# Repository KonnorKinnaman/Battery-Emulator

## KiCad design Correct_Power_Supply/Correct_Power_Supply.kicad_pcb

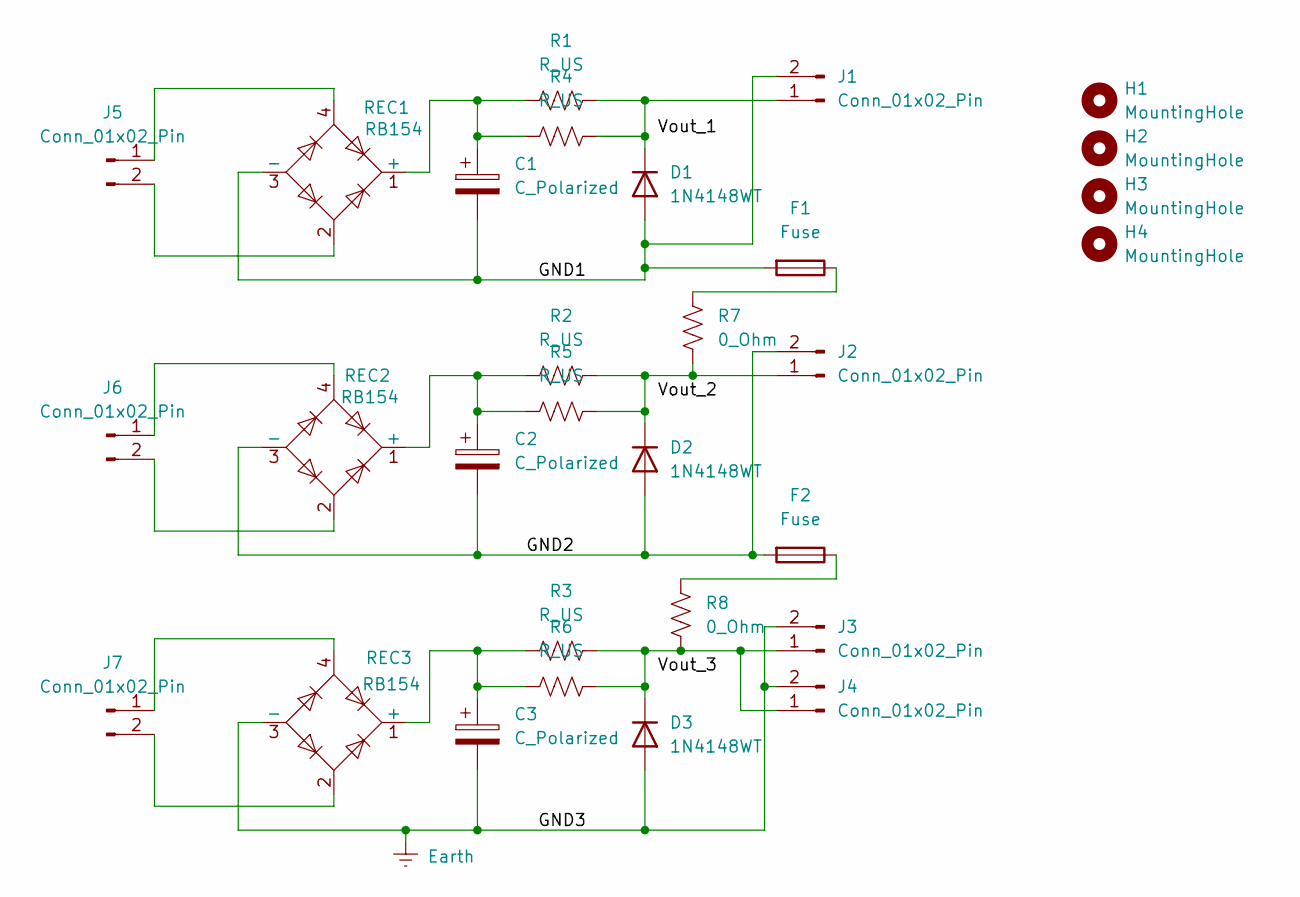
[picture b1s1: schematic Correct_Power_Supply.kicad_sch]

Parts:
C1, C2, C3: C_Polarized; CP_Radial_D8.0mm_P5.00mm
D1, D2, D3: 1N4148WT; D_A-405_P7.62mm_Horizontal
F1, F2: Fuse; SS5H2AAPH
H1, H2, H3, H4: MountingHole; MountingHole_2.2mm_M2_DIN965_Pad
J1, J2, J3, J4, J5, J6, J7: Conn_01x02_Pin; PinHeader_1x02_P2.54mm_Vertical
R1, R2, R3, R4, R5, R6: R_US; R_Axial_DIN0204_L3.6mm_D1.6mm_P5.08mm_Horizontal
R7, R8: 0_Ohm; R_Axial_DIN0204_L3.6mm_D1.6mm_P5.08mm_Horizontal
REC1, REC2, REC3: RB154; Diode_Bridge_Round_D9.0mm

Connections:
/GND1: C1.2, D1.2 (A), F1.2, J1.2, REC1.3 (-)
/GND2: C2.2, D2.2 (A), F2.2, J2.2, REC2.3 (-)
Earth: C3.2, D3.2 (A), J3.2, J4.2, REC3.3 (-)
unnamed: D1.1 (K), J1.1, R1.1, R4.1
unnamed: D2.1 (K), J2.1, R2.1, R5.1, R7.1
unnamed: D3.1 (K), J3.1, J4.1, R3.1, R6.1, R8.1
unnamed: F1.1, R7.2
unnamed: F2.1, R8.2
unnamed: J5.1, REC1.4
unnamed: J5.2, REC1.2
unnamed: J6.1, REC2.4
unnamed: J6.2, REC2.2
unnamed: J7.1, REC3.4
unnamed: J7.2, REC3.2
unnamed: C1.1, R1.2, R4.2, REC1.1 (+)
unnamed: C2.1, R2.2, R5.2, REC2.1 (+)
unnamed: C3.1, R3.2, R6.2, REC3.1 (+)

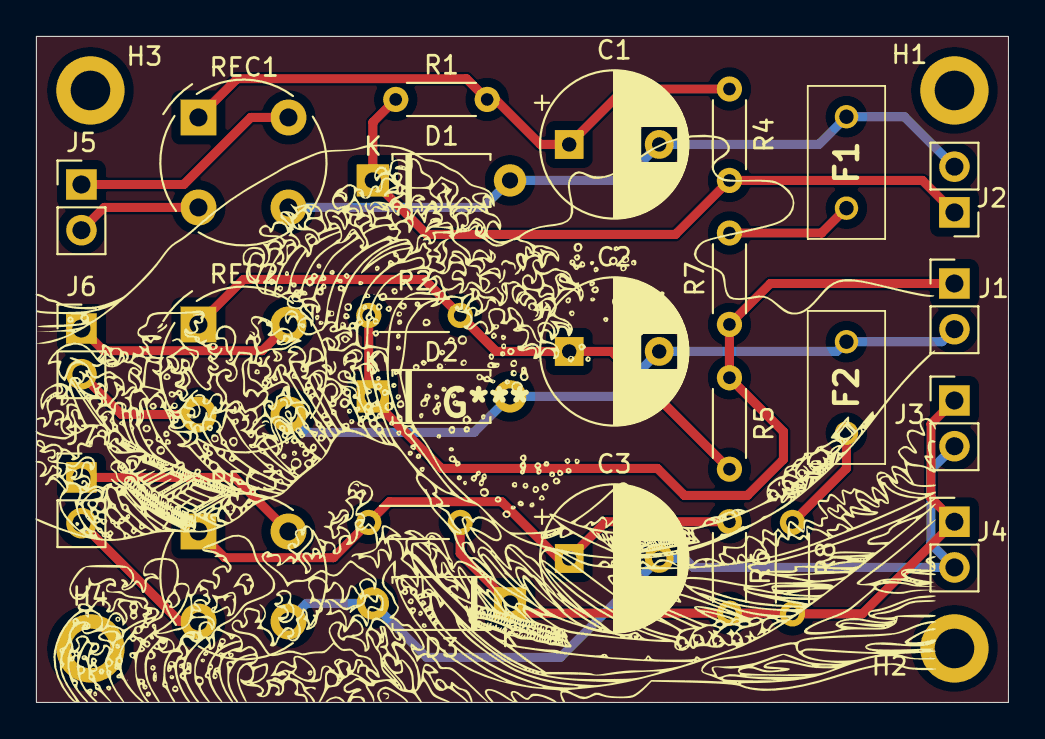
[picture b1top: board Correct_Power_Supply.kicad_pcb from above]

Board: 2 copper layers, 54.0 x 37.0 mm, 30 parts (0 on the bottom side), 17 nets.

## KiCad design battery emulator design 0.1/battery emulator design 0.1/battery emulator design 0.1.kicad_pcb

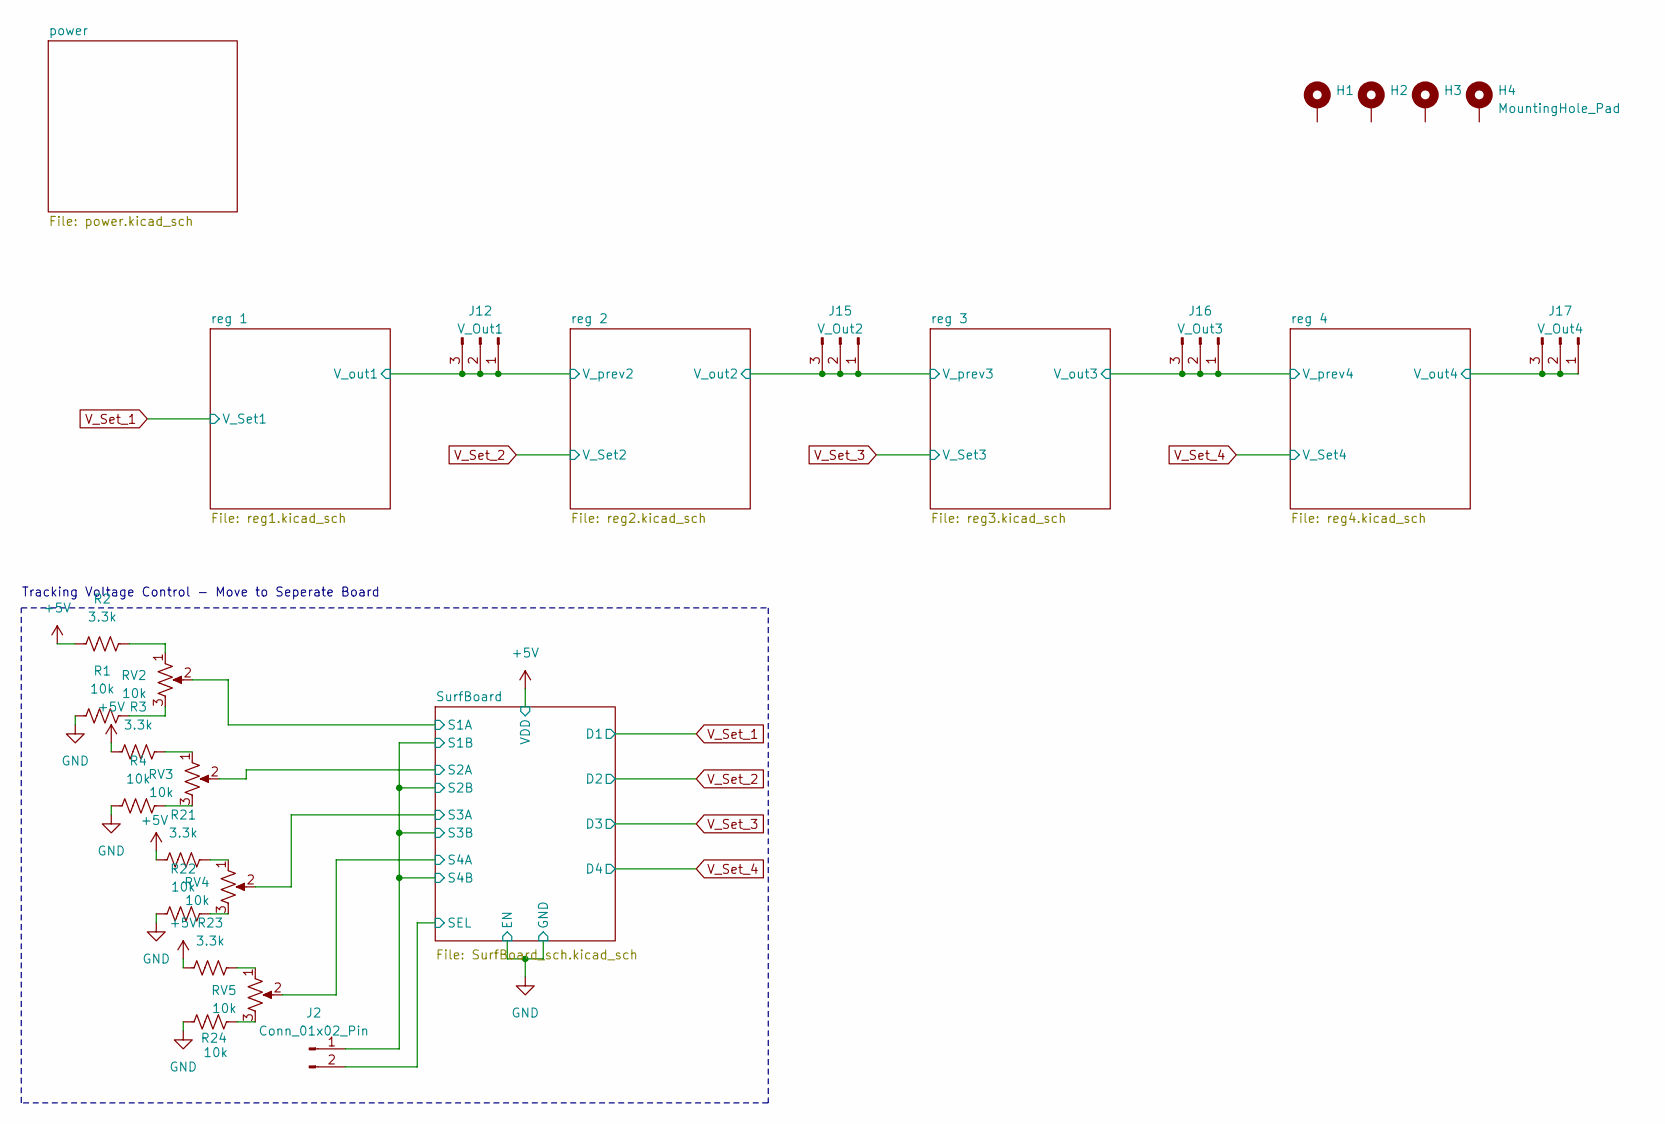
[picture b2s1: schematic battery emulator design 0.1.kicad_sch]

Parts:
H1, H2, H3, H4: MountingHole_Pad; MountingHole_4.3mm_M4_Pad
J2: Conn_01x02_Pin; PinHeader_1x02_P2.54mm_Vertical
J12: V_Out1; PinHeader_1x03_P2.54mm_Vertical
J15: V_Out2; PinHeader_1x03_P2.54mm_Vertical
J16: V_Out3; PinHeader_1x03_P2.54mm_Vertical
J17: V_Out4; PinHeader_1x03_P2.54mm_Vertical
R1, R4, R22, R24: 10k; R_Axial_DIN0207_L6.3mm_D2.5mm_P10.16mm_Horizontal
R2, R3, R21, R23: 3.3k; R_Axial_DIN0207_L6.3mm_D2.5mm_P10.16mm_Horizontal
RV2, RV3, RV4, RV5: 10k; PDB181

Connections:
+5V: R2.2, R3.2, R21.2, R23.2; also elsewhere on the board
/SurfBoard/S1A: RV2.2; also elsewhere on the board
/SurfBoard/S1B: J2.1; also elsewhere on the board
/SurfBoard/S2A: RV3.2; also elsewhere on the board
/SurfBoard/S3A: RV4.2; also elsewhere on the board
/SurfBoard/S4A: RV5.2; also elsewhere on the board
/SurfBoard/SEL: J2.2; also elsewhere on the board
/reg 1/V_out1: J12.1, J12.2, J12.3; also elsewhere on the board
/reg 2/V_out2: J15.1, J15.2, J15.3; also elsewhere on the board
/reg 3/V_out3: J16.1, J16.2, J16.3; also elsewhere on the board
/reg 4/V_out4: J17.1, J17.2, J17.3; also elsewhere on the board
GND: R1.2, R4.2, R22.2, R24.2; also elsewhere on the board
unnamed: R1.1, RV2.3
unnamed: R2.1, RV2.1
unnamed: R3.1, RV3.1
unnamed: R4.1, RV3.3
unnamed: R21.1, RV4.1
unnamed: R22.1, RV4.3
unnamed: R23.1, RV5.1
unnamed: R24.1, RV5.3

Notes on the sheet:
Tracking Voltage Control - Move to Seperate Board

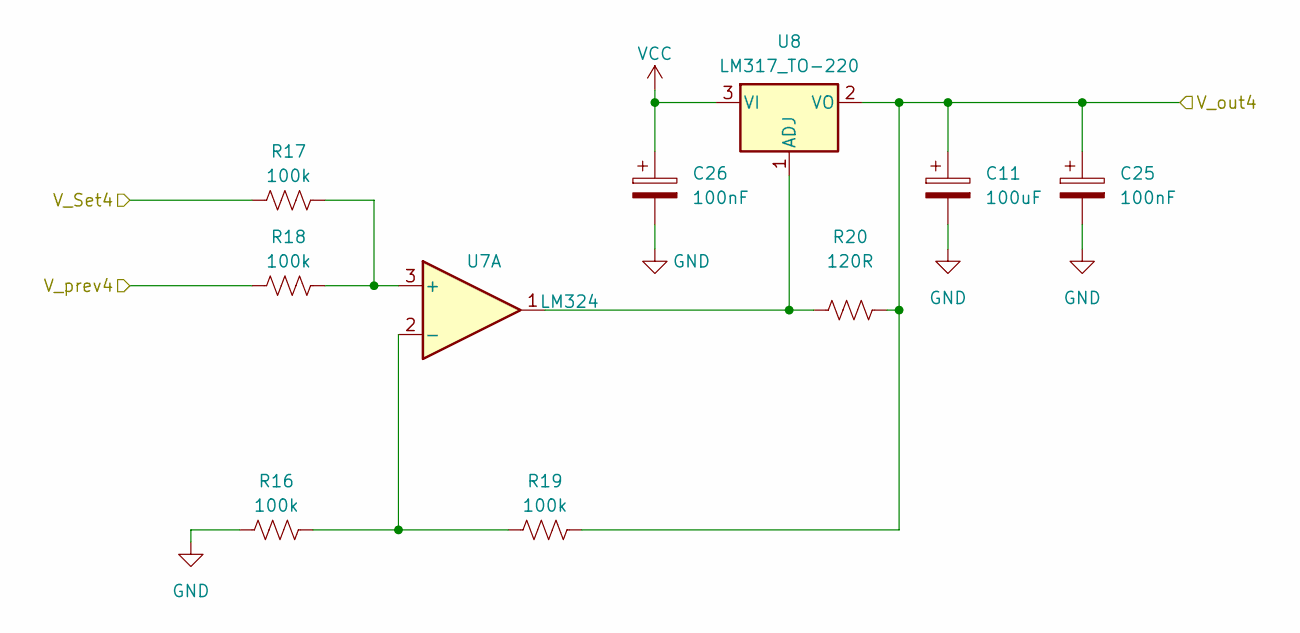
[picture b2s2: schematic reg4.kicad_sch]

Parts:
C11: 100uF; CP_Radial_D7.5mm_P2.50mm
C25, C26: 100nF; C_Disc_D3.4mm_W2.1mm_P2.50mm
R16, R17, R18, R19: 100k; R_Axial_DIN0207_L6.3mm_D2.5mm_P10.16mm_Horizontal
R20: 120R; R_Axial_DIN0207_L6.3mm_D2.5mm_P10.16mm_Horizontal
U7: LM324; DIP-8_W7.62mm_LongPads
U8: LM317_TO-220; TO-220-3_Vertical

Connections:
/reg 3/V_out3: R18.1; also elsewhere on the board
/reg 4/V_out4: C11.1, C25.1, R19.2, R20.1, U8.2 (VO); also elsewhere on the board
GND: C11.2, C25.2, C26.2, R16.1; also elsewhere on the board
unnamed 26: R17.2, R18.2, U7.3 (+); also elsewhere on the board
unnamed 27: R16.2, R19.1, U7.2 (-); also elsewhere on the board
unnamed 31: R20.2, U7.1, U8.1 (ADJ); also elsewhere on the board
VCC: C26.1, U8.3 (VI); also elsewhere on the board
V_Set_4: R17.1; also elsewhere on the board

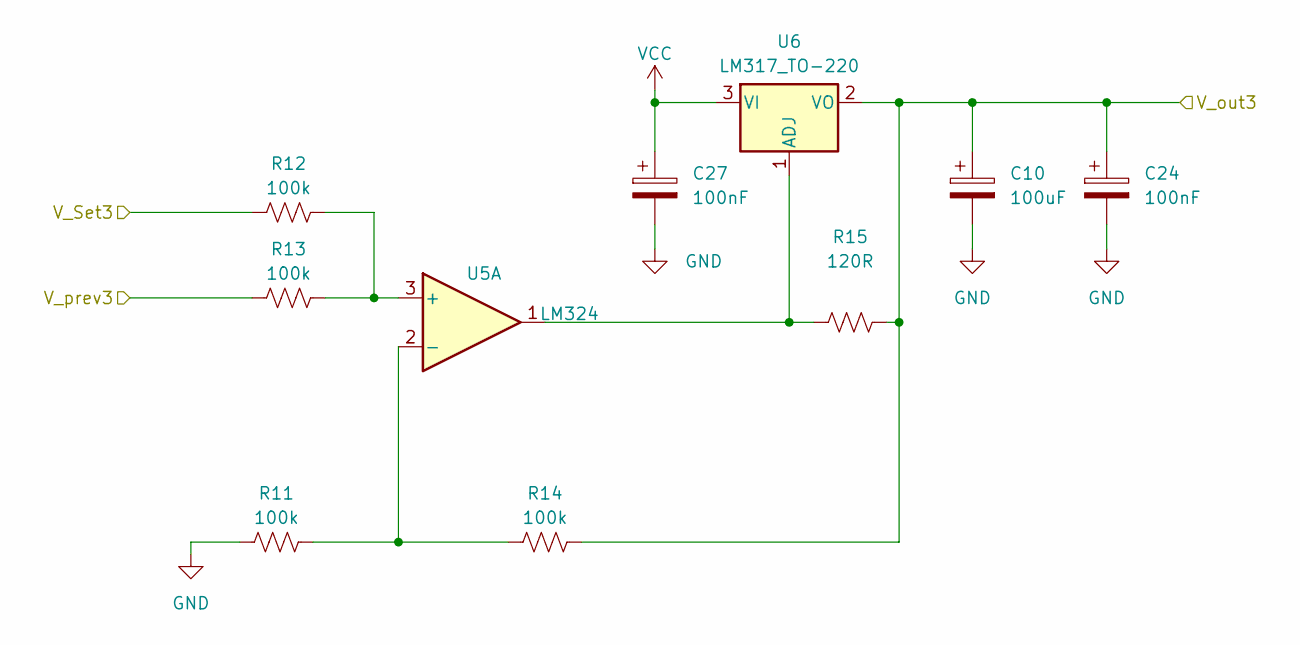
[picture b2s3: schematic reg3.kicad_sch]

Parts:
C10: 100uF; CP_Radial_D7.5mm_P2.50mm
C24, C27: 100nF; C_Disc_D3.4mm_W2.1mm_P2.50mm
R11, R12, R13, R14: 100k; R_Axial_DIN0207_L6.3mm_D2.5mm_P10.16mm_Horizontal
R15: 120R; R_Axial_DIN0207_L6.3mm_D2.5mm_P10.16mm_Horizontal
U5: LM324; DIP-8_W7.62mm_LongPads
U6: LM317_TO-220; TO-220-3_Vertical

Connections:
/reg 2/V_out2: R13.1; also elsewhere on the board
/reg 3/V_out3: C10.1, C24.1, R14.2, R15.1, U6.2 (VO); also elsewhere on the board
GND: C10.2, C24.2, C27.2, R11.1; also elsewhere on the board
unnamed 24: R12.2, R13.2, U5.3 (+); also elsewhere on the board
unnamed 25: R11.2, R14.1, U5.2 (-); also elsewhere on the board
unnamed 30: R15.2, U5.1, U6.1 (ADJ); also elsewhere on the board
VCC: C27.1, U6.3 (VI); also elsewhere on the board
V_Set_3: R12.1; also elsewhere on the board

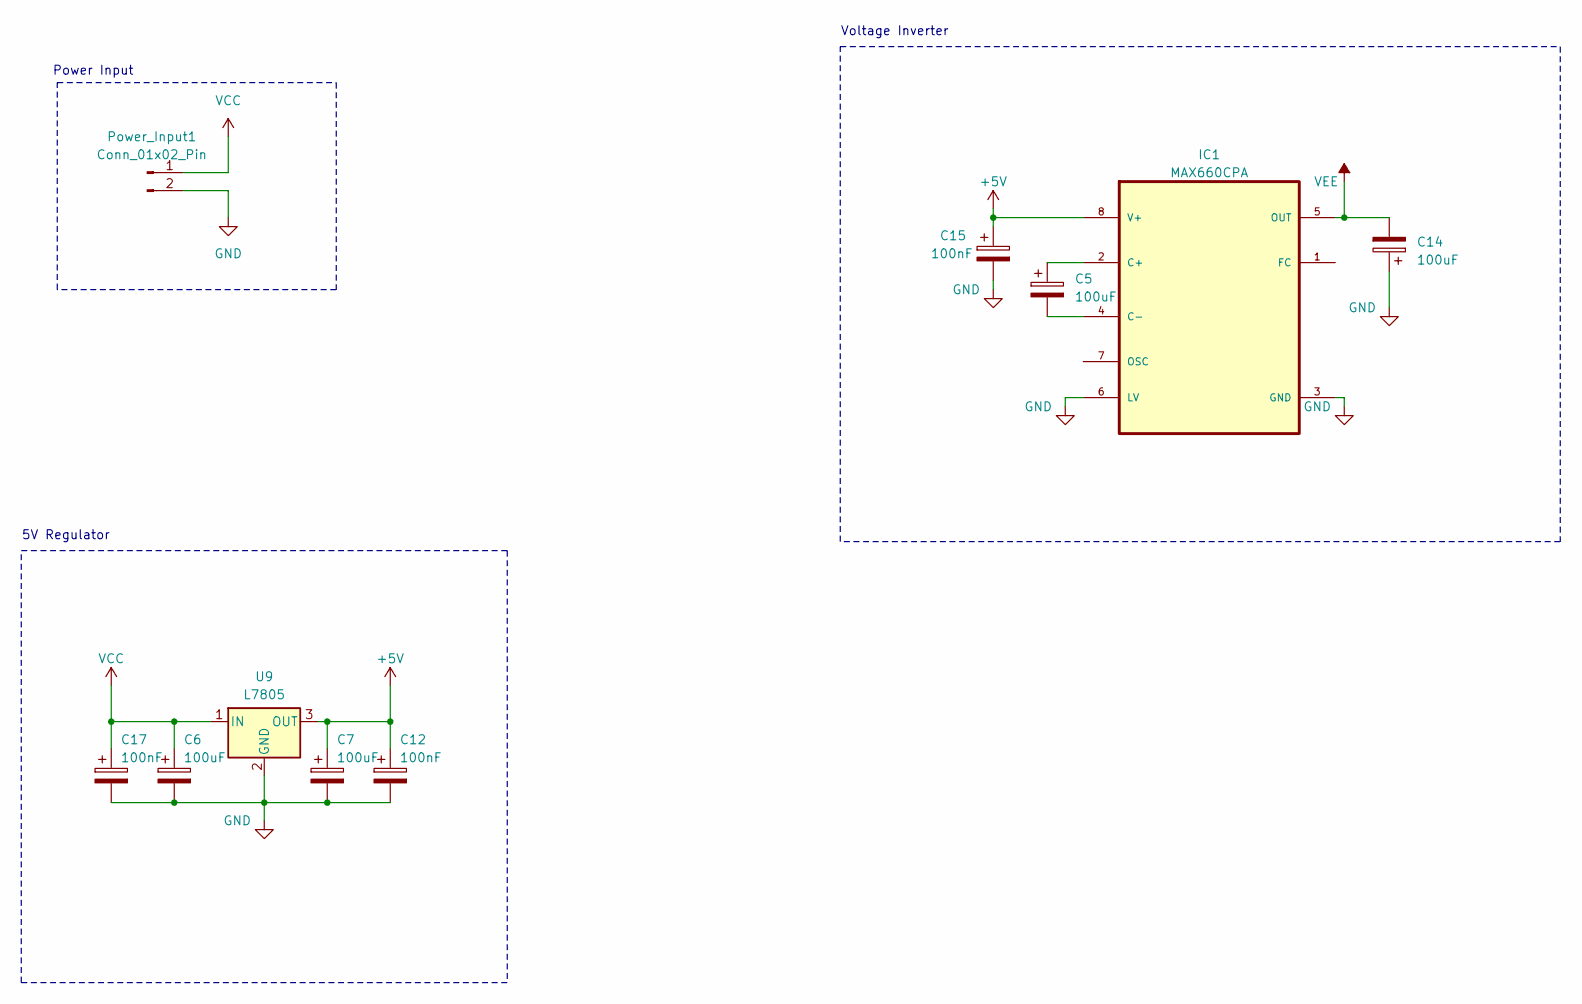
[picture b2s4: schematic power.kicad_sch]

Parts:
C5, C6, C7, C14: 100uF; CP_Radial_D7.5mm_P2.50mm
C12, C15, C17: 100nF; C_Disc_D4.3mm_W1.9mm_P5.00mm
IC1: MAX660CPA; DIP-8_W7.62mm_LongPads
Power_Input1: Conn_01x02_Pin; PinHeader_1x02_P2.54mm_Vertical
U9: L7805; TO-220-3_Vertical

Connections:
+5V: C7.1, C12.1, C15.1, IC1.8 (V+), U9.3 (OUT); also elsewhere on the board
GND: C6.2, C7.2, C12.2, C14.1, C15.2, C17.2, IC1.3 (GND), IC1.6 (LV), Power_Input1.2, U9.2 (GND); also elsewhere on the board
unnamed: C5.1, IC1.2 (C+)
unnamed: C5.2, IC1.4 (C-)
VCC: C6.1, C17.1, Power_Input1.1, U9.1 (IN); also elsewhere on the board
VEE: C14.2, IC1.5 (OUT); also elsewhere on the board

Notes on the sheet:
Voltage Inverter
5V Regulator
Power Input

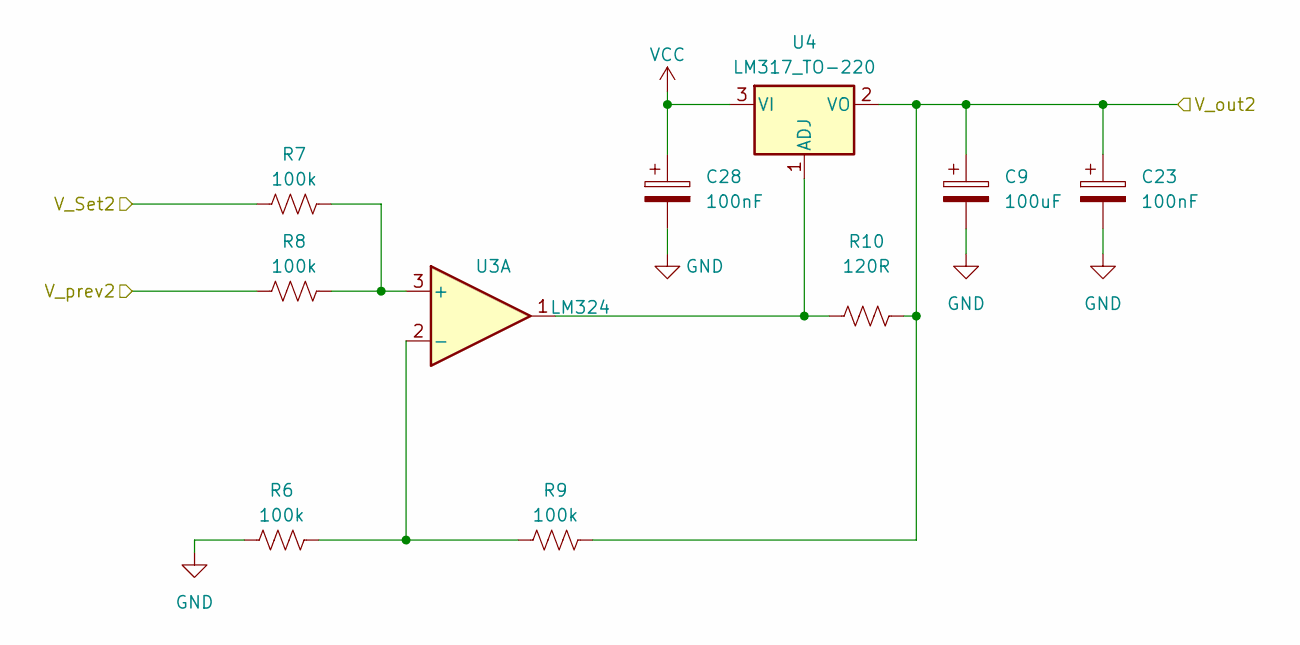
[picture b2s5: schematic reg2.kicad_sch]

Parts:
C9: 100uF; CP_Radial_D7.5mm_P2.50mm
C23, C28: 100nF; C_Disc_D3.4mm_W2.1mm_P2.50mm
R6, R7, R8, R9: 100k; R_Axial_DIN0207_L6.3mm_D2.5mm_P10.16mm_Horizontal
R10: 120R; R_Axial_DIN0207_L6.3mm_D2.5mm_P10.16mm_Horizontal
U3: LM324; DIP-8_W7.62mm_LongPads
U4: LM317_TO-220; TO-220-3_Vertical

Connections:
/reg 1/V_out1: R8.1; also elsewhere on the board
/reg 2/V_out2: C9.1, C23.1, R9.2, R10.1, U4.2 (VO); also elsewhere on the board
GND: C9.2, C23.2, C28.2, R6.1; also elsewhere on the board
unnamed 22: R7.2, R8.2, U3.3 (+); also elsewhere on the board
unnamed 23: R6.2, R9.1, U3.2 (-); also elsewhere on the board
unnamed 29: R10.2, U3.1, U4.1 (ADJ); also elsewhere on the board
VCC: C28.1, U4.3 (VI); also elsewhere on the board
V_Set_2: R7.1; also elsewhere on the board

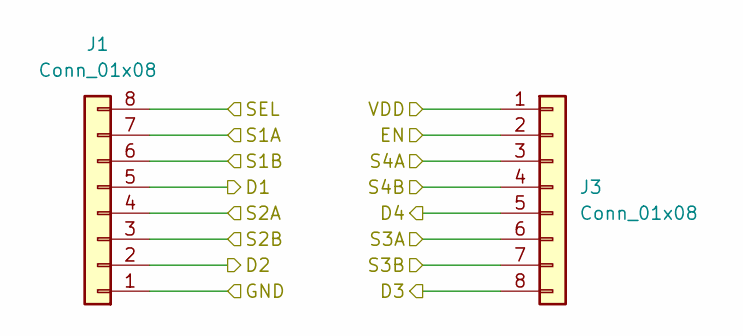
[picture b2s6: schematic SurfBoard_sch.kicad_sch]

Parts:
J1, J3: Conn_01x08; PinSocket_1x08_P2.54mm_Vertical

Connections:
+5V: J3.1; also elsewhere on the board
/SurfBoard/S1A: J1.7; also elsewhere on the board
/SurfBoard/S1B: J1.3, J1.6, J3.4, J3.7; also elsewhere on the board
/SurfBoard/S2A: J1.4; also elsewhere on the board
/SurfBoard/S3A: J3.6; also elsewhere on the board
/SurfBoard/S4A: J3.3; also elsewhere on the board
/SurfBoard/SEL: J1.8; also elsewhere on the board
GND: J1.1, J3.2; also elsewhere on the board
V_Set_1: J1.5; also elsewhere on the board
V_Set_2: J1.2; also elsewhere on the board
V_Set_3: J3.8; also elsewhere on the board
V_Set_4: J3.5; also elsewhere on the board

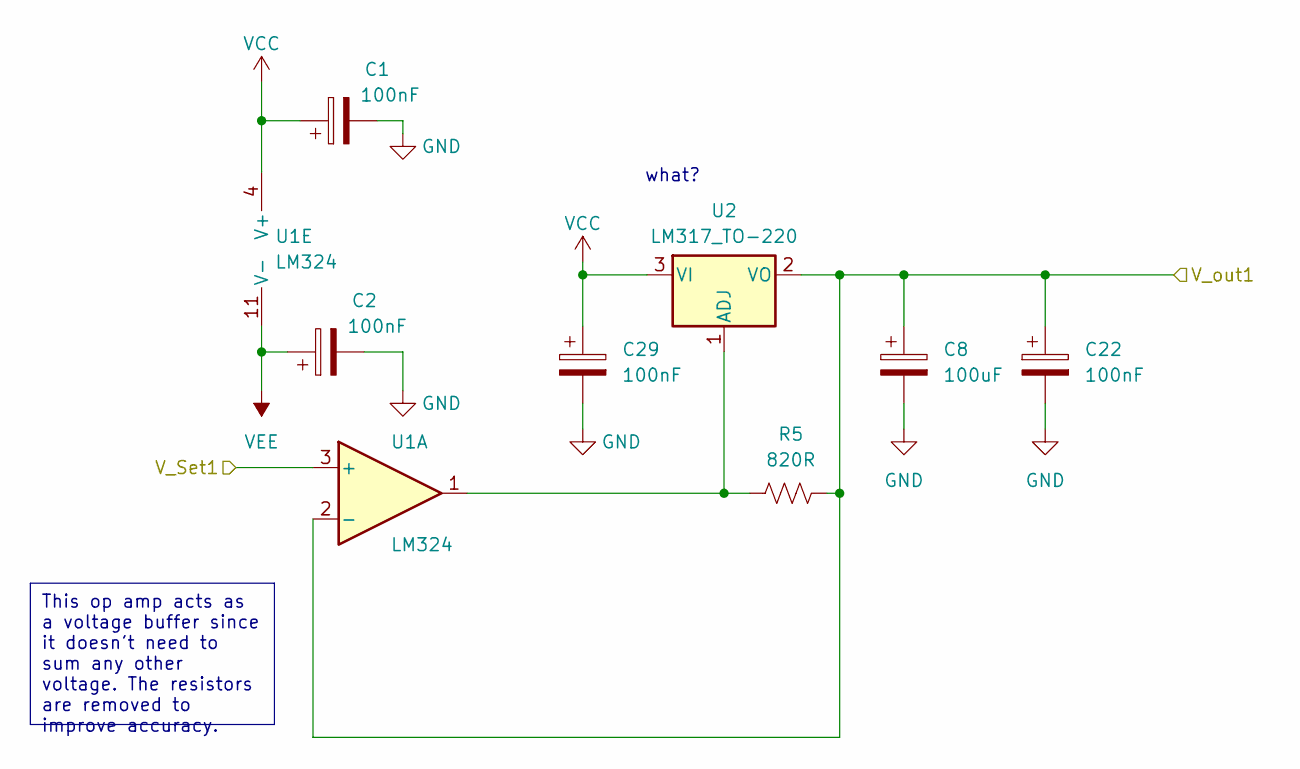
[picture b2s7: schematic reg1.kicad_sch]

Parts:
C1, C2, C22, C29: 100nF; C_Disc_D3.4mm_W2.1mm_P2.50mm
C8: 100uF; CP_Radial_D7.5mm_P2.50mm
R5: 820R; R_Axial_DIN0207_L6.3mm_D2.5mm_P10.16mm_Horizontal
U1: LM324; DIP-8_W7.62mm_LongPads
U2: LM317_TO-220; TO-220-3_Vertical

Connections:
/reg 1/V_out1: C8.1, C22.1, R5.1, U1.2 (-), U2.2 (VO); also elsewhere on the board
GND: C1.2, C2.2, C8.2, C22.2, C29.2; also elsewhere on the board
unnamed 22: U1.5 (+); also elsewhere on the board
unnamed 23: U1.6 (-); also elsewhere on the board
unnamed 24: U1.10 (+); also elsewhere on the board
unnamed 25: U1.9 (-); also elsewhere on the board
unnamed 26: U1.12 (+); also elsewhere on the board
unnamed 27: U1.13 (-); also elsewhere on the board
unnamed: R5.2, U1.1, U2.1 (ADJ)
unnamed 29: U1.7; also elsewhere on the board
unnamed 30: U1.8; also elsewhere on the board
unnamed 31: U1.14; also elsewhere on the board
VCC: C1.1, C29.1, U1.4 (V+), U2.3 (VI); also elsewhere on the board
VEE: C2.1, U1.11 (V-); also elsewhere on the board
V_Set_1: U1.3 (+); also elsewhere on the board

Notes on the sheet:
This op amp acts as a voltage buffer since it doesn't need to sum any other voltage. The resistors are removed to improve accuracy.
what?

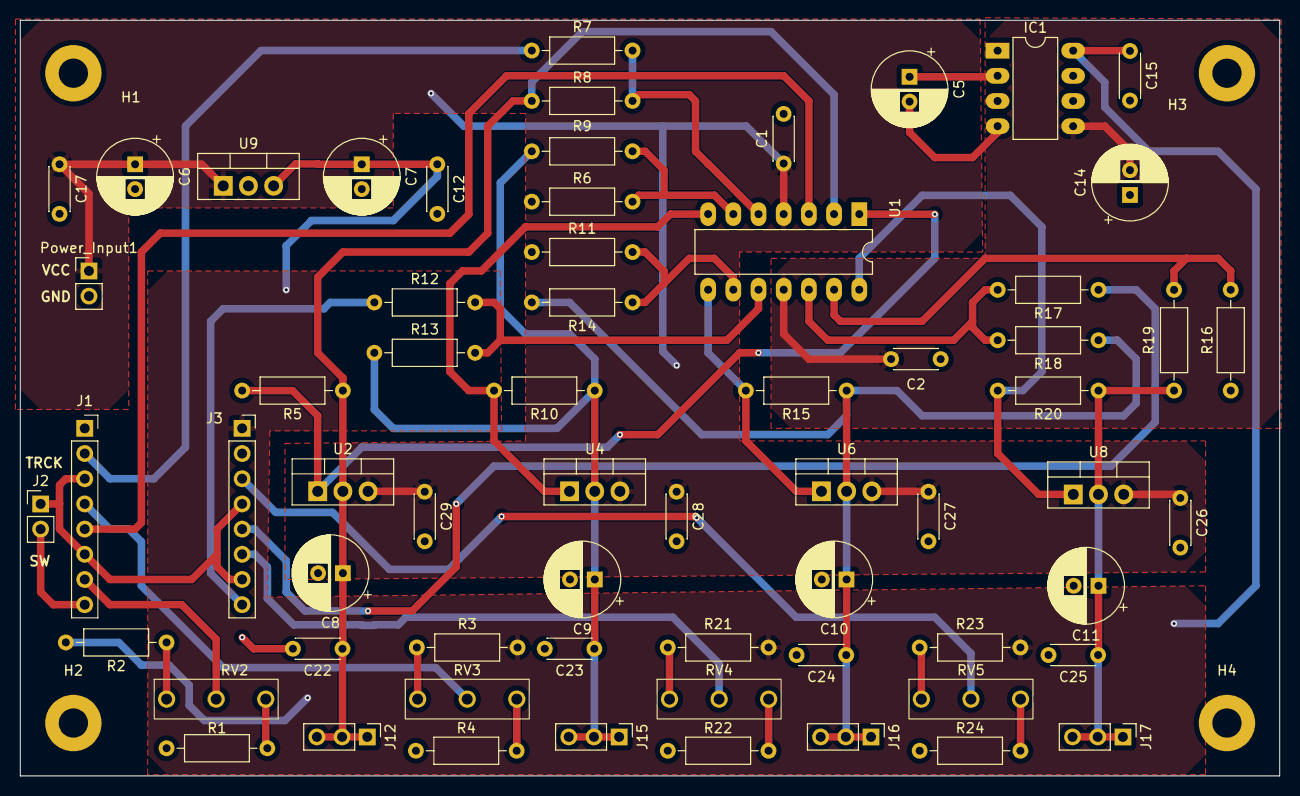
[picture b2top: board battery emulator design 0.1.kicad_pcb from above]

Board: 2 copper layers, 127.0 x 76.2 mm, 68 parts (0 on the bottom side), 38 nets.

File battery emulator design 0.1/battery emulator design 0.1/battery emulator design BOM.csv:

Reference,Value,Datasheet,Footprint,Qty,DNP
"C1,C2,C12,C15,C17,C22,C23,C24,C25,C26,C27,C28,C29",100nF,~,Capacitor_THT:C_Disc_D4.3mm_W1.9mm_P5.00mm,13,
"C5,C6,C7,C8,C9,C10,C11,C14",100uF,~,Capacitor_THT:CP_Radial_D7.5mm_P2.50mm,8,
"H1,H2,H3,H4",MountingHole_Pad,~,MountingHole:MountingHole_4.3mm_M4_Pad,4,
IC1,MAX660CPA,,Package_DIP:DIP-8_W7.62mm_LongPads,1,
"J1,J3",Conn_01x08,~,Connector_PinSocket_2.54mm:PinSocket_1x08_P2.54mm_Vertical,2,
"J2,Power_Input1",Conn_01x02_Pin,~,Connector_PinHeader_2.54mm:PinHeader_1x02_P2.54mm_Vertical,2,
J12,V_Out1,~,Connector_PinHeader_2.54mm:PinHeader_1x03_P2.54mm_Vertical,1,
J15,V_Out2,~,Connector_PinHeader_2.54mm:PinHeader_1x03_P2.54mm_Vertical,1,
J16,V_Out3,~,Connector_PinHeader_2.54mm:PinHeader_1x03_P2.54mm_Vertical,1,
J17,V_Out4,~,Connector_PinHeader_2.54mm:PinHeader_1x03_P2.54mm_Vertical,1,
"R1,R4,R22,R24,RV2,RV3,RV4,RV5",10k,~,"Resistor_THT:R_Axial_DIN0207_L6.3mm_D2.5mm_P10.16mm_Horizontal,battery_emulator:PDB181",8,
"R2,R3,R21,R23",3.3k,~,Resistor_THT:R_Axial_DIN0207_L6.3mm_D2.5mm_P10.16mm_Horizontal,4,
"R5,R10,R15,R20",150,~,Resistor_THT:R_Axial_DIN0207_L6.3mm_D2.5mm_P10.16mm_Horizontal,1,
"R6,R7,R8,R9,R11,R12,R13,R14,R16,R17,R18,R19",100k,~,Resistor_THT:R_Axial_DIN0207_L6.3mm_D2.5mm_P10.16mm_Horizontal,12,
U1,LM324,http://www.ti.com/lit/ds/symlink/lm2902-n.pdf,Package_DIP:DIP-14_W7.62mm_LongPads,1,
"U2,U4,U6,U8",LM317_TO-220,http://www.ti.com/lit/ds/symlink/lm317.pdf,Package_TO_SOT_THT:TO-220-3_Vertical,4,
U9,L7805,http://www.st.com/content/ccc/resource/technical/document/da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,Package_TO_SOT_THT:TO-220-3_Vertical,1,

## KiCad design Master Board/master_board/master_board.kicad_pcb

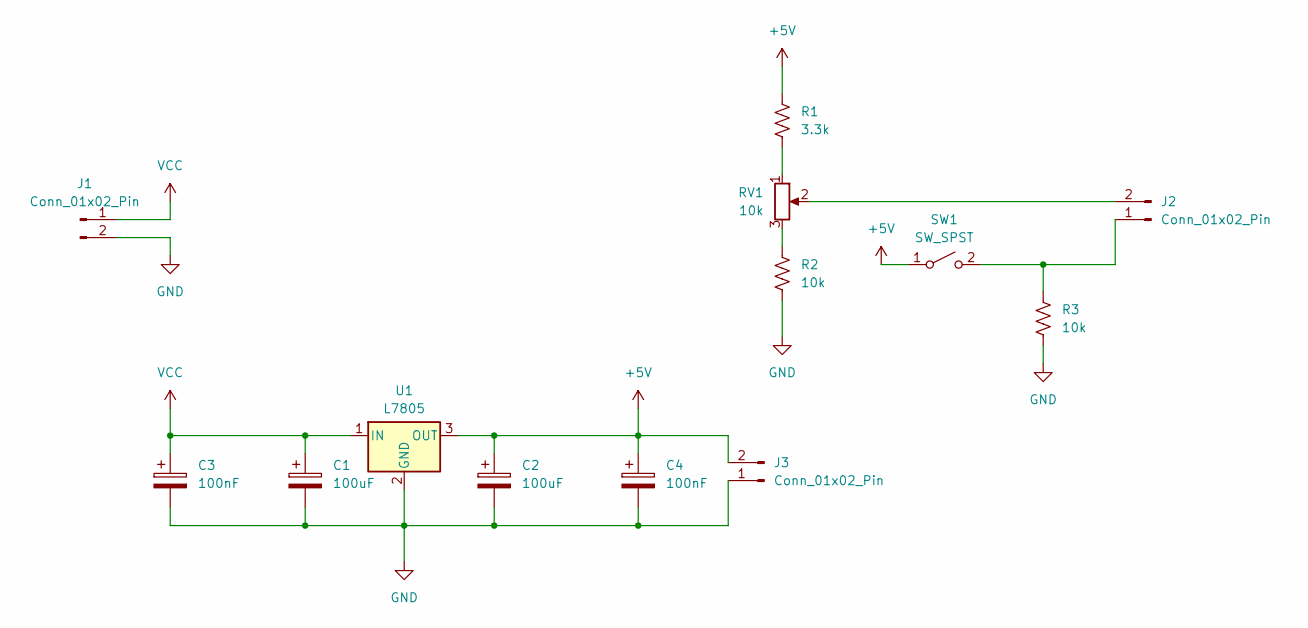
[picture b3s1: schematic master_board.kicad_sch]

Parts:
C1, C2: 100uF; CP_Radial_D6.3mm_P2.50mm
C3, C4: 100nF; C_Disc_D4.7mm_W2.5mm_P5.00mm
J1, J2, J3: Conn_01x02_Pin; PinHeader_1x02_P2.54mm_Vertical
R1: 3.3k; R_Axial_DIN0207_L6.3mm_D2.5mm_P10.16mm_Horizontal
R2, R3: 10k; R_Axial_DIN0207_L6.3mm_D2.5mm_P10.16mm_Horizontal
RV1: 10k; PDB181
SW1: SW_SPST; PinHeader_1x02_P2.54mm_Vertical
U1: L7805; TO-220-3_Vertical

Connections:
+5V: C2.1, C4.1, J3.2, R1.1, SW1.1 (A), U1.3 (OUT)
GND: C1.2, C2.2, C3.2, C4.2, J1.2, J3.1, R2.2, R3.2, U1.2 (GND)
unnamed: J2.1, R3.1, SW1.2 (B)
unnamed: J2.2, RV1.2
unnamed: R1.2, RV1.1
unnamed: R2.1, RV1.3
VCC: C1.1, C3.1, J1.1, U1.1 (IN)

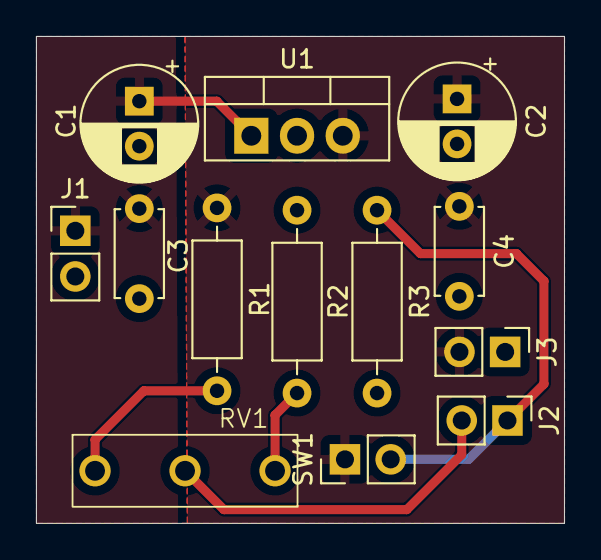
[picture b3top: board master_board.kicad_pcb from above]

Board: 2 copper layers, 29.3 x 27.1 mm, 13 parts (0 on the bottom side), 7 nets.

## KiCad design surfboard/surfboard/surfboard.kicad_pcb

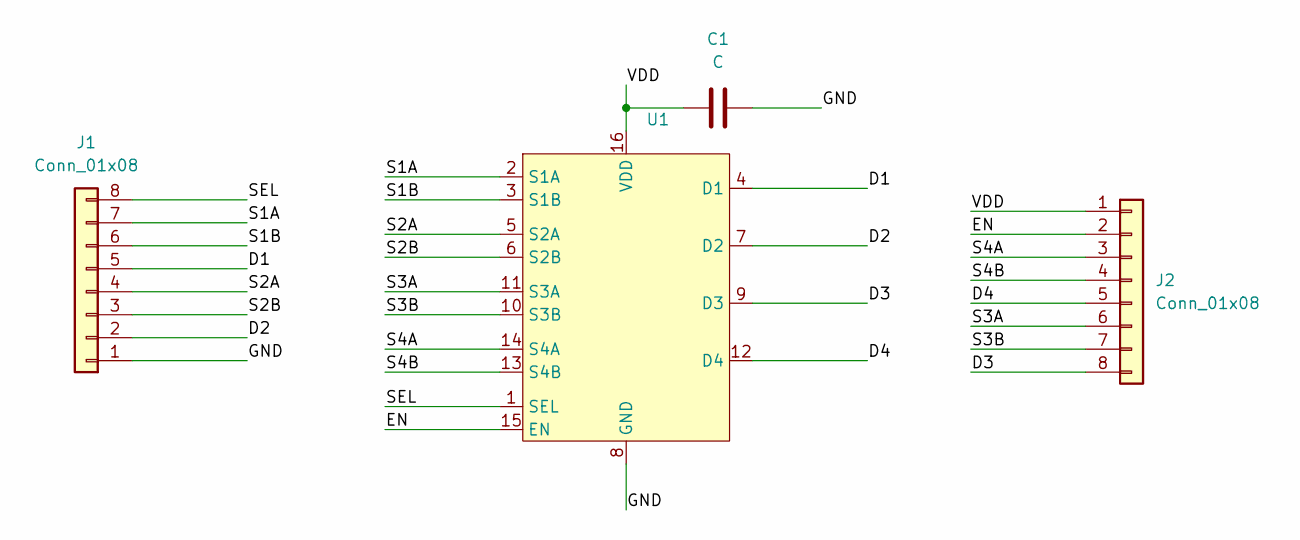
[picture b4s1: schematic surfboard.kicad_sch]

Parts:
C1: C; C_Disc_D3.0mm_W1.6mm_P2.50mm
J1, J2: Conn_01x08; PinHeader_1x08_P2.54mm_Vertical
U1: SOIC_PRQ1_TEX-L

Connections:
/D1: J1.5, U1.4 (D1)
/D2: J1.2, U1.7 (D2)
/D3: J2.8, U1.9 (D3)
/D4: J2.5, U1.12 (D4)
/EN: J2.2, U1.15 (EN)
/GND: C1.1, J1.1, U1.8 (GND)
/S1A: J1.7, U1.2 (S1A)
/S1B: J1.6, U1.3 (S1B)
/S2A: J1.4, U1.5 (S2A)
/S2B: J1.3, U1.6 (S2B)
/S3A: J2.6, U1.11 (S3A)
/S3B: J2.7, U1.10 (S3B)
/S4A: J2.3, U1.14 (S4A)
/S4B: J2.4, U1.13 (S4B)
/SEL: J1.8, U1.1 (SEL)
/VDD: C1.2, J2.1, U1.16 (VDD)

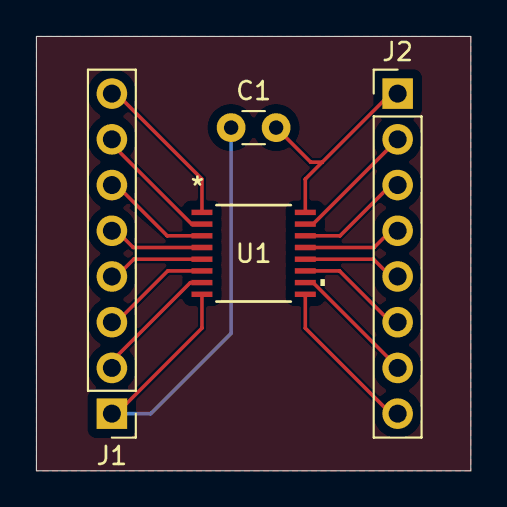
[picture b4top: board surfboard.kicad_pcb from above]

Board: 2 copper layers, 24.1 x 24.1 mm, 4 parts (0 on the bottom side), 16 nets.

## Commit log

2025-02-04 adding all exisiting files
2025-02-08 added pots to voltage buffers, other minor changes
2025-02-11 Deletus that pcbus
2025-04-29 updating with all other boards
